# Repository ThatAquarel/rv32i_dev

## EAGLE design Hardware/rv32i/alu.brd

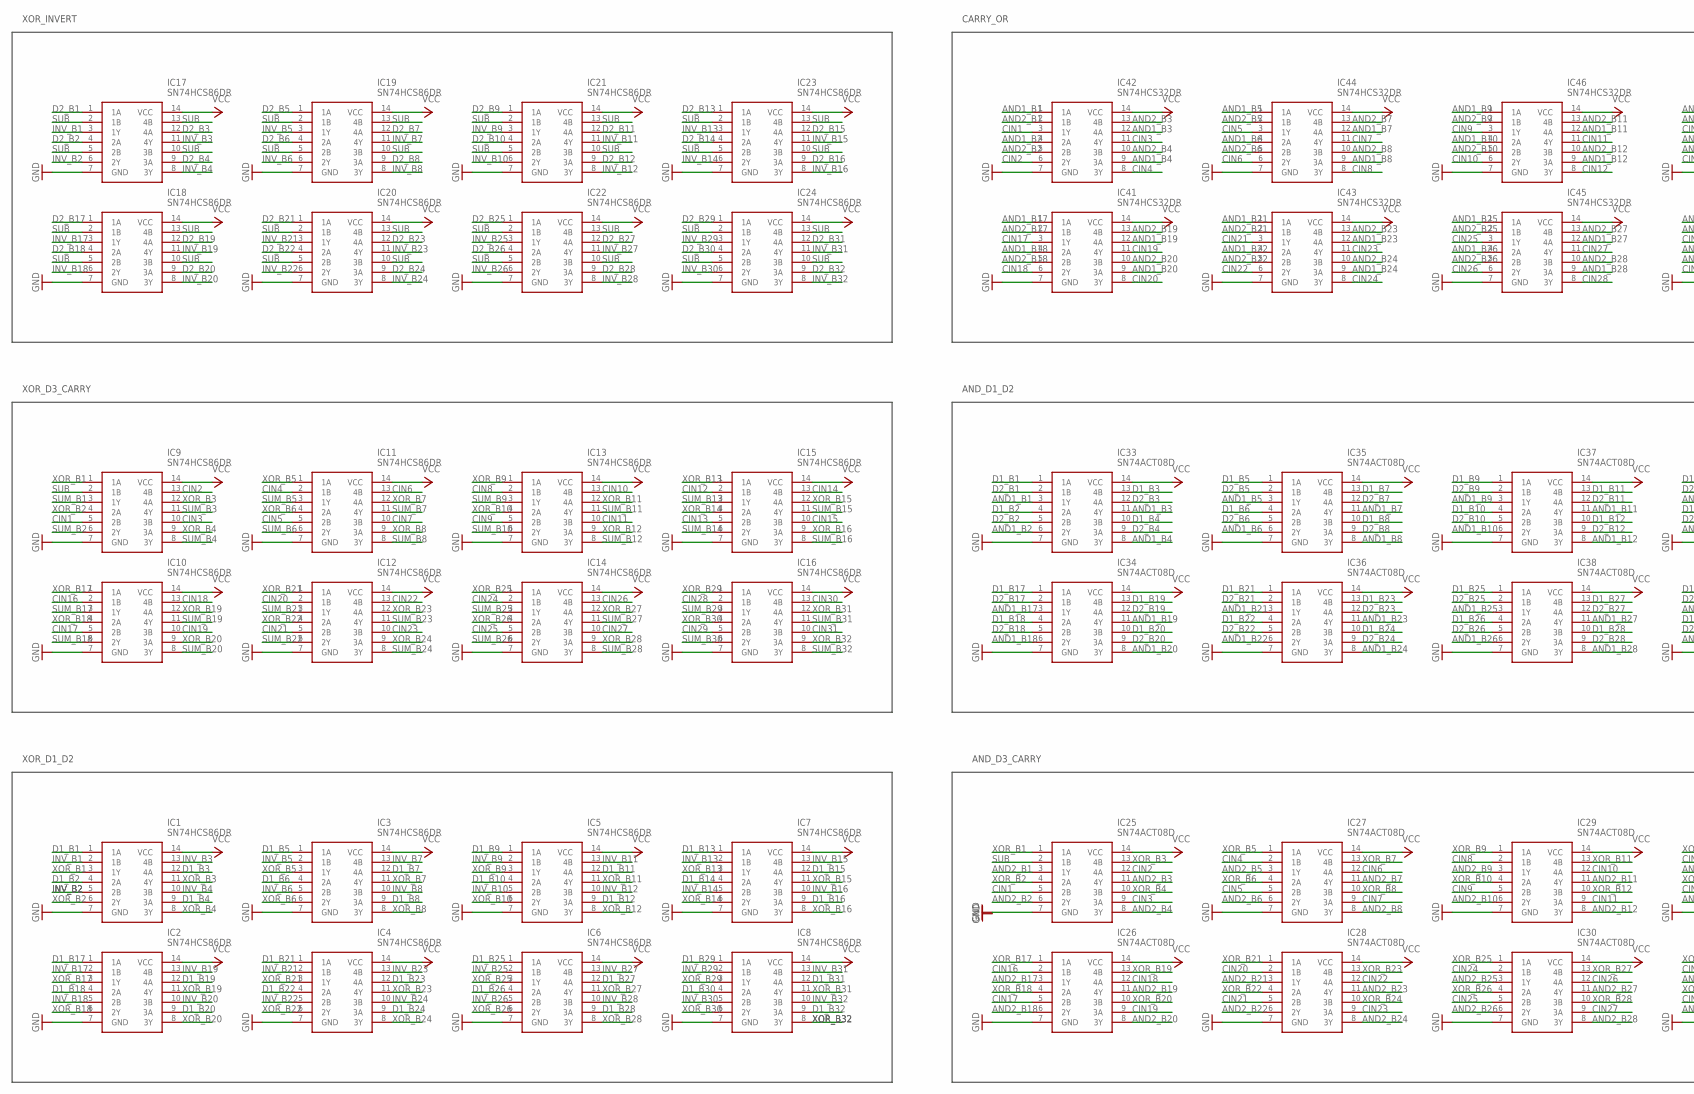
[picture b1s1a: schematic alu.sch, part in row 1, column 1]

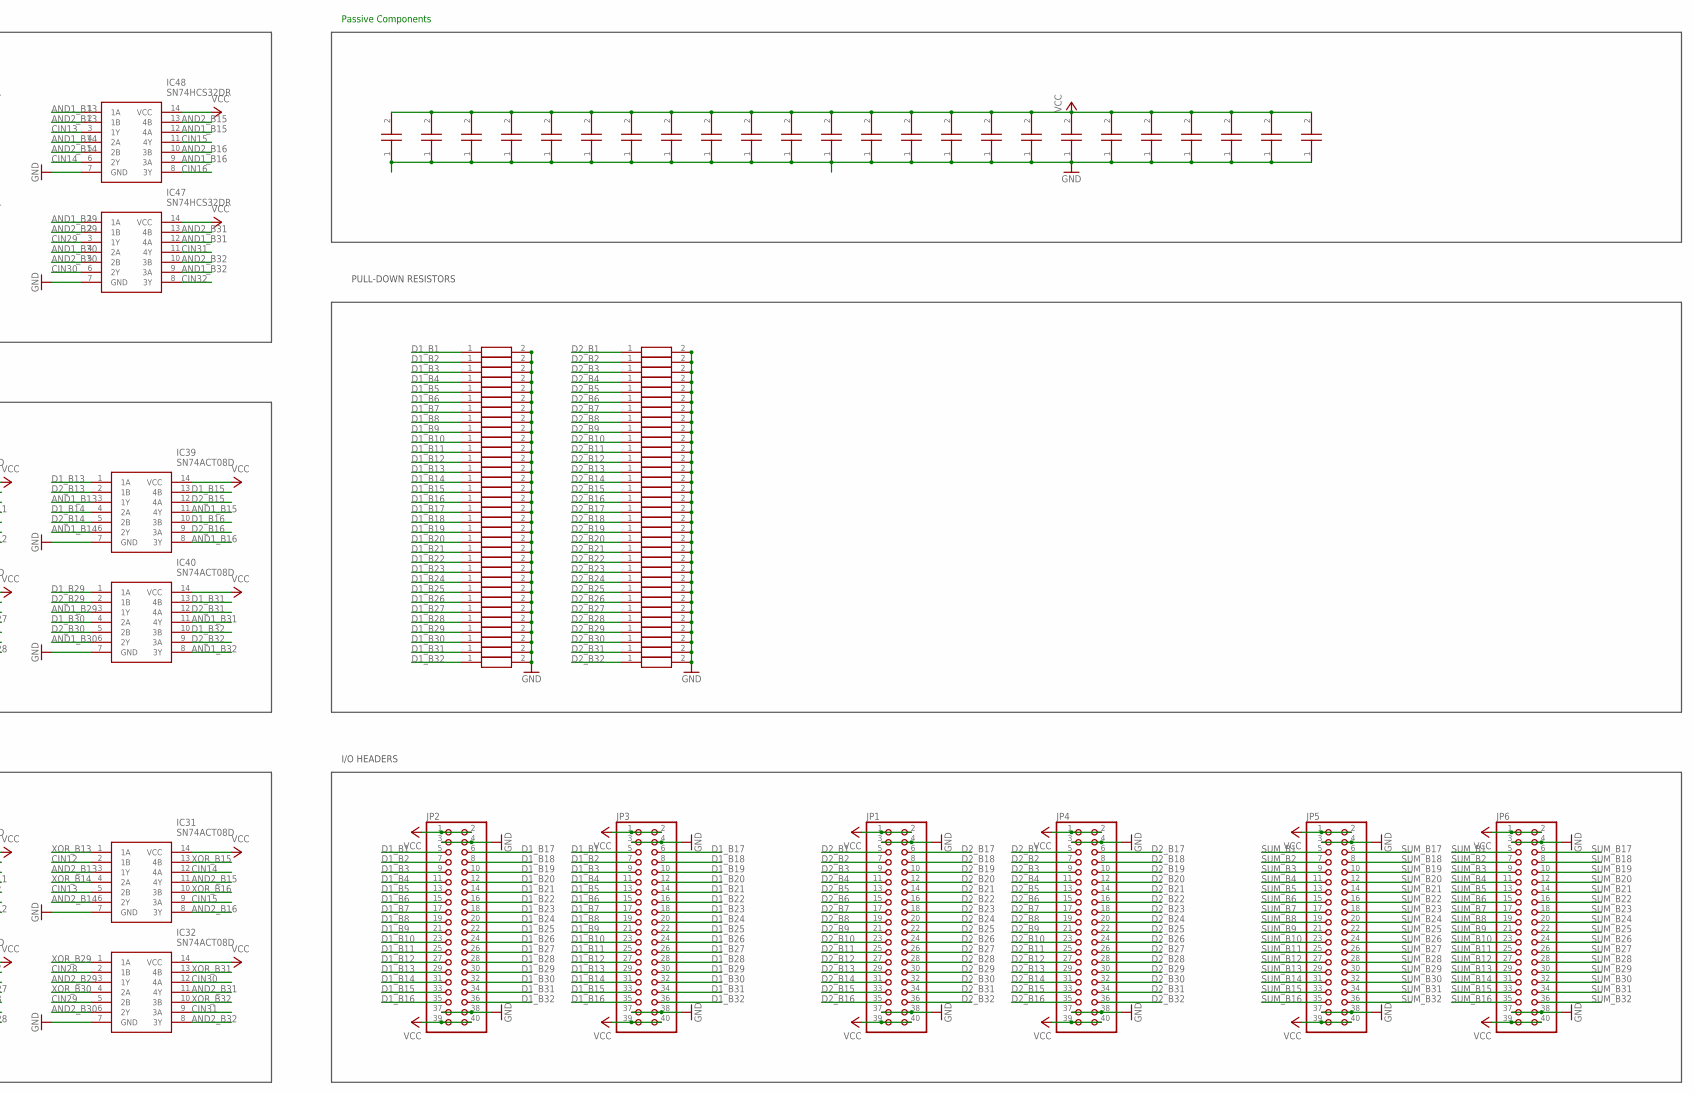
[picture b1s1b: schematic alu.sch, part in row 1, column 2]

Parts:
C1, C2, C3, C4, C5, C6, C7, C8, C9, C10, C11, C12, C13, C14, C15, C16, C17, C18, C19, C20, C21, C22, C23, C24: CC0603KRX7R9BB104; CAPC1608X90N
IC1, IC2, IC3, IC4, IC5, IC6, IC7, IC8, IC9, IC10, IC11, IC12, IC13, IC14, IC15, IC16, IC17, IC18, IC19, IC20, IC21, IC22, IC23, IC24: SN74HCS86DR; SOIC127P600X175-14N
IC25, IC26, IC27, IC28, IC29, IC30, IC31, IC32, IC33, IC34, IC35, IC36, IC37, IC38, IC39, IC40: SN74ACT08D; SOIC127P600X175-14N
IC41, IC42, IC43, IC44, IC45, IC46, IC47, IC48: SN74HCS32DR; SOIC127P600X175-14N
JP1, JP2, JP3, JP4, JP5, JP6: PINHD-2X20; 2X20
R1, R2, R3, R4, R5, R6, R7, R8, R9, R10, R11, R12, R13, R14, R15, R16, R17, R18, R19, R20, R21, R22, R23, R24, R25, R26, R27, R28, R29, R30, R31, R32, R33, R34, R35, R36, R37, R38, R39, R40, R41, R42, R43, R44, R45, R46, R47, R48, R49, R50, R51, R52, R53, R54, R55, R56, R57, R58, R59, R60, R61, R62, R63, R64: RC0603FR-0710KL; RESC1608X55N

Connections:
AND1_B1: IC33.3 (1Y), IC42.1 (1A)
AND1_B2: IC33.6 (2Y), IC42.4 (2A)
AND1_B3: IC33.11 (4Y), IC42.12 (4A)
AND1_B4: IC33.8 (3Y), IC42.9 (3A)
AND1_B5: IC35.3 (1Y), IC44.1 (1A)
AND1_B6: IC35.6 (2Y), IC44.4 (2A)
AND1_B7: IC35.11 (4Y), IC44.12 (4A)
AND1_B8: IC35.8 (3Y), IC44.9 (3A)
AND1_B9: IC37.3 (1Y), IC46.1 (1A)
AND1_B10: IC37.6 (2Y), IC46.4 (2A)
AND1_B11: IC37.11 (4Y), IC46.12 (4A)
AND1_B12: IC37.8 (3Y), IC46.9 (3A)
AND1_B13: IC39.3 (1Y), IC48.1 (1A)
AND1_B14: IC39.6 (2Y), IC48.4 (2A)
AND1_B15: IC39.11 (4Y), IC48.12 (4A)
AND1_B16: IC39.8 (3Y), IC48.9 (3A)
AND1_B17: IC34.3 (1Y), IC41.1 (1A)
AND1_B18: IC34.6 (2Y), IC41.4 (2A)
AND1_B19: IC34.11 (4Y), IC41.12 (4A)
AND1_B20: IC34.8 (3Y), IC41.9 (3A)
AND1_B21: IC36.3 (1Y), IC43.1 (1A)
AND1_B22: IC36.6 (2Y), IC43.4 (2A)
AND1_B23: IC36.11 (4Y), IC43.12 (4A)
AND1_B24: IC36.8 (3Y), IC43.9 (3A)
AND1_B25: IC38.3 (1Y), IC45.1 (1A)
AND1_B26: IC38.6 (2Y), IC45.4 (2A)
AND1_B27: IC38.11 (4Y), IC45.12 (4A)
AND1_B28: IC38.8 (3Y), IC45.9 (3A)
AND1_B29: IC40.3 (1Y), IC47.1 (1A)
AND1_B30: IC40.6 (2Y), IC47.4 (2A)
AND1_B31: IC40.11 (4Y), IC47.12 (4A)
AND1_B32: IC40.8 (3Y), IC47.9 (3A)
AND2_B1: IC25.3 (1Y), IC42.2 (1B)
AND2_B2: IC25.6 (2Y), IC42.5 (2B)
AND2_B3: IC25.11 (4Y), IC42.13 (4B)
AND2_B4: IC25.8 (3Y), IC42.10 (3B)
AND2_B5: IC27.3 (1Y), IC44.2 (1B)
AND2_B6: IC27.6 (2Y), IC44.5 (2B)
AND2_B7: IC27.11 (4Y), IC44.13 (4B)
AND2_B8: IC27.8 (3Y), IC44.10 (3B)
AND2_B9: IC29.3 (1Y), IC46.2 (1B)
AND2_B10: IC29.6 (2Y), IC46.5 (2B)
AND2_B11: IC29.11 (4Y), IC46.13 (4B)
AND2_B12: IC29.8 (3Y), IC46.10 (3B)
AND2_B13: IC31.3 (1Y), IC48.2 (1B)
AND2_B14: IC31.6 (2Y), IC48.5 (2B)
AND2_B15: IC31.11 (4Y), IC48.13 (4B)
AND2_B16: IC31.8 (3Y), IC48.10 (3B)
AND2_B17: IC26.3 (1Y), IC41.2 (1B)
AND2_B18: IC26.6 (2Y), IC41.5 (2B)
AND2_B19: IC26.11 (4Y), IC41.13 (4B)
AND2_B20: IC26.8 (3Y), IC41.10 (3B)
AND2_B21: IC28.3 (1Y), IC43.2 (1B)
AND2_B22: IC28.6 (2Y), IC43.5 (2B)
AND2_B23: IC28.11 (4Y), IC43.13 (4B)
AND2_B24: IC28.8 (3Y), IC43.10 (3B)
AND2_B25: IC30.3 (1Y), IC45.2 (1B)
AND2_B26: IC30.6 (2Y), IC45.5 (2B)
AND2_B27: IC30.11 (4Y), IC45.13 (4B)
AND2_B28: IC30.8 (3Y), IC45.10 (3B)
AND2_B29: IC32.3 (1Y), IC47.2 (1B)
AND2_B30: IC32.6 (2Y), IC47.5 (2B)
AND2_B31: IC32.11 (4Y), IC47.13 (4B)
AND2_B32: IC32.8 (3Y), IC47.10 (3B)
CIN1: IC9.5 (2B), IC25.5 (2B), IC42.3 (1Y)
CIN2: IC9.13 (4B), IC25.12 (4A), IC42.6 (2Y)
CIN3: IC9.10 (3B), IC25.9 (3A), IC42.11 (4Y)
CIN4: IC11.2 (1B), IC27.2 (1B), IC42.8 (3Y)
CIN5: IC11.5 (2B), IC27.5 (2B), IC44.3 (1Y)
CIN6: IC11.13 (4B), IC27.12 (4A), IC44.6 (2Y)
CIN7: IC11.10 (3B), IC27.9 (3A), IC44.11 (4Y)
CIN8: IC13.2 (1B), IC29.2 (1B), IC44.8 (3Y)
CIN9: IC13.5 (2B), IC29.5 (2B), IC46.3 (1Y)
CIN10: IC13.13 (4B), IC29.12 (4A), IC46.6 (2Y)
CIN11: IC13.10 (3B), IC29.9 (3A), IC46.11 (4Y)
CIN12: IC15.2 (1B), IC31.2 (1B), IC46.8 (3Y)
CIN13: IC15.5 (2B), IC31.5 (2B), IC48.3 (1Y)
CIN14: IC15.13 (4B), IC31.12 (4A), IC48.6 (2Y)
CIN15: IC15.10 (3B), IC31.9 (3A), IC48.11 (4Y)
CIN16: IC10.2 (1B), IC26.2 (1B), IC48.8 (3Y)
CIN17: IC10.5 (2B), IC26.5 (2B), IC41.3 (1Y)
CIN18: IC10.13 (4B), IC26.12 (4A), IC41.6 (2Y)
CIN19: IC10.10 (3B), IC26.9 (3A), IC41.11 (4Y)
CIN20: IC12.2 (1B), IC28.2 (1B), IC41.8 (3Y)
CIN21: IC12.5 (2B), IC28.5 (2B), IC43.3 (1Y)
CIN22: IC12.13 (4B), IC28.12 (4A), IC43.6 (2Y)
CIN23: IC12.10 (3B), IC28.9 (3A), IC43.11 (4Y)
CIN24: IC14.2 (1B), IC30.2 (1B), IC43.8 (3Y)
CIN25: IC14.5 (2B), IC30.5 (2B), IC45.3 (1Y)
CIN26: IC14.13 (4B), IC30.12 (4A), IC45.6 (2Y)
CIN27: IC14.10 (3B), IC30.9 (3A), IC45.11 (4Y)
CIN28: IC16.2 (1B), IC32.2 (1B), IC45.8 (3Y)
CIN29: IC16.5 (2B), IC32.5 (2B), IC47.3 (1Y)
CIN30: IC16.13 (4B), IC32.12 (4A), IC47.6 (2Y)
CIN31: IC16.10 (3B), IC32.9 (3A), IC47.11 (4Y)
CIN32: IC47.8 (3Y)
D1_B1: IC1.1 (1A), IC33.1 (1A), JP2.5, JP3.5, R1.1
D1_B2: IC1.4 (2A), IC33.4 (2A), JP2.7, JP3.7, R2.1
D1_B3: IC1.12 (4A), IC33.13 (4B), JP2.9, JP3.9, R3.1
D1_B4: IC1.9 (3A), IC33.10 (3B), JP2.11, JP3.11, R4.1
D1_B5: IC3.1 (1A), IC35.1 (1A), JP2.13, JP3.13, R5.1
D1_B6: IC3.4 (2A), IC35.4 (2A), JP2.15, JP3.15, R6.1
D1_B7: IC3.12 (4A), IC35.13 (4B), JP2.17, JP3.17, R7.1
D1_B8: IC3.9 (3A), IC35.10 (3B), JP2.19, JP3.19, R8.1
D1_B9: IC5.1 (1A), IC37.1 (1A), JP2.21, JP3.21, R9.1
D1_B10: IC5.4 (2A), IC37.4 (2A), JP2.23, JP3.23, R10.1
D1_B11: IC5.12 (4A), IC37.13 (4B), JP2.25, JP3.25, R11.1
D1_B12: IC5.9 (3A), IC37.10 (3B), JP2.27, JP3.27, R12.1
D1_B13: IC7.1 (1A), IC39.1 (1A), JP2.29, JP3.29, R13.1
D1_B14: IC7.4 (2A), IC39.4 (2A), JP2.31, JP3.31, R14.1
D1_B15: IC7.12 (4A), IC39.13 (4B), JP2.33, JP3.33, R15.1
D1_B16: IC7.9 (3A), IC39.10 (3B), JP2.35, JP3.35, R17.1
D1_B17: IC2.1 (1A), IC34.1 (1A), JP2.6, JP3.6, R16.1
D1_B18: IC2.4 (2A), IC34.4 (2A), JP2.8, JP3.8, R18.1
D1_B19: IC2.12 (4A), IC34.13 (4B), JP2.10, JP3.10, R19.1
D1_B20: IC2.9 (3A), IC34.10 (3B), JP2.12, JP3.12, R20.1
D1_B21: IC4.1 (1A), IC36.1 (1A), JP2.14, JP3.14, R21.1
D1_B22: IC4.4 (2A), IC36.4 (2A), JP2.16, JP3.16, R22.1
D1_B23: IC4.12 (4A), IC36.13 (4B), JP2.18, JP3.18, R23.1
D1_B24: IC4.9 (3A), IC36.10 (3B), JP2.20, JP3.20, R24.1
D1_B25: IC6.1 (1A), IC38.1 (1A), JP2.22, JP3.22, R26.1
D1_B26: IC6.4 (2A), IC38.4 (2A), JP2.24, JP3.24, R25.1
D1_B27: IC6.12 (4A), IC38.13 (4B), JP2.26, JP3.26, R27.1
D1_B28: IC6.9 (3A), IC38.10 (3B), JP2.28, JP3.28, R28.1
D1_B29: IC8.1 (1A), IC40.1 (1A), JP2.30, JP3.30, R29.1
D1_B30: IC8.4 (2A), IC40.4 (2A), JP2.32, JP3.32, R30.1
D1_B31: IC8.12 (4A), IC40.13 (4B), JP2.34, JP3.34, R31.1
D1_B32: IC8.9 (3A), IC40.10 (3B), JP2.36, JP3.36, R32.1
D2_B1: IC17.1 (1A), IC33.2 (1B), JP1.5, JP4.5, R33.1
D2_B2: IC17.4 (2A), IC33.5 (2B), JP1.7, JP4.7, R34.1
D2_B3: IC17.12 (4A), IC33.12 (4A), JP1.9, JP4.9, R35.1
D2_B4: IC17.9 (3A), IC33.9 (3A), JP1.11, JP4.11, R36.1
D2_B5: IC19.1 (1A), IC35.2 (1B), JP1.13, JP4.13, R37.1
D2_B6: IC19.4 (2A), IC35.5 (2B), JP1.15, JP4.15, R38.1
D2_B7: IC19.12 (4A), IC35.12 (4A), JP1.17, JP4.17, R39.1
D2_B8: IC19.9 (3A), IC35.9 (3A), JP1.19, JP4.19, R40.1
D2_B9: IC21.1 (1A), IC37.2 (1B), JP1.21, JP4.21, R41.1
D2_B10: IC21.4 (2A), IC37.5 (2B), JP1.23, JP4.23, R42.1
D2_B11: IC21.12 (4A), IC37.12 (4A), JP1.25, JP4.25, R43.1
D2_B12: IC21.9 (3A), IC37.9 (3A), JP1.27, JP4.27, R44.1
D2_B13: IC23.1 (1A), IC39.2 (1B), JP1.29, JP4.29, R45.1
D2_B14: IC23.4 (2A), IC39.5 (2B), JP1.31, JP4.31, R46.1
D2_B15: IC23.12 (4A), IC39.12 (4A), JP1.33, JP4.33, R47.1
D2_B16: IC23.9 (3A), IC39.9 (3A), JP1.35, JP4.35, R49.1
D2_B17: IC18.1 (1A), IC34.2 (1B), JP1.6, JP4.6, R48.1
D2_B18: IC18.4 (2A), IC34.5 (2B), JP1.8, JP4.8, R50.1
D2_B19: IC18.12 (4A), IC34.12 (4A), JP1.10, JP4.10, R51.1
D2_B20: IC18.9 (3A), IC34.9 (3A), JP1.12, JP4.12, R52.1
D2_B21: IC20.1 (1A), IC36.2 (1B), JP1.14, JP4.14, R53.1
D2_B22: IC20.4 (2A), IC36.5 (2B), JP1.16, JP4.16, R54.1
D2_B23: IC20.12 (4A), IC36.12 (4A), JP1.18, JP4.18, R55.1
D2_B24: IC20.9 (3A), IC36.9 (3A), JP1.20, JP4.20, R56.1
D2_B25: IC22.1 (1A), IC38.2 (1B), JP1.22, JP4.22, R58.1
D2_B26: IC22.4 (2A), IC38.5 (2B), JP1.24, JP4.24, R57.1
D2_B27: IC22.12 (4A), IC38.12 (4A), JP1.26, JP4.26, R59.1
D2_B28: IC22.9 (3A), IC38.9 (3A), JP1.28, JP4.28, R60.1
D2_B29: IC24.1 (1A), IC40.2 (1B), JP1.30, JP4.30, R61.1
D2_B30: IC24.4 (2A), IC40.5 (2B), JP1.32, JP4.32, R62.1
D2_B31: IC24.12 (4A), IC40.12 (4A), JP1.34, JP4.34, R63.1
D2_B32: IC24.9 (3A), IC40.9 (3A), JP1.36, JP4.36, R64.1
GND: C1.1, C2.1, C3.1, C4.1, C5.1, C6.1, C7.1, C8.1, C9.1, C10.1, C11.1, C12.1, C13.1, C14.1, C15.1, C16.1, C17.1, C18.1, C19.1, C20.1, C21.1, C22.1, C23.1, C24.1, IC1.7 (GND), IC2.7 (GND), IC3.7 (GND), IC4.7 (GND), IC5.7 (GND), IC6.7 (GND), IC7.7 (GND), IC8.7 (GND), IC9.7 (GND), IC10.7 (GND), IC11.7 (GND), IC12.7 (GND), IC13.7 (GND), IC14.7 (GND), IC15.7 (GND), IC16.7 (GND), IC17.7 (GND), IC18.7 (GND), IC19.7 (GND), IC20.7 (GND), IC21.7 (GND), IC22.7 (GND), IC23.7 (GND), IC24.7 (GND), IC25.7 (GND), IC26.7 (GND), IC27.7 (GND), IC28.7 (GND), IC29.7 (GND), IC30.7 (GND), IC31.7 (GND), IC32.7 (GND), IC33.7 (GND), IC34.7 (GND), IC35.7 (GND), IC36.7 (GND), IC37.7 (GND), IC38.7 (GND), IC39.7 (GND), IC40.7 (GND), IC41.7 (GND), IC42.7 (GND), IC43.7 (GND), IC44.7 (GND), IC45.7 (GND), IC46.7 (GND), IC47.7 (GND), IC48.7 (GND), JP1.3, JP1.4, JP1.37, JP1.38, JP2.3, JP2.4, JP2.37, JP2.38, JP3.3, JP3.4, JP3.37, JP3.38, JP4.3, JP4.4, JP4.37, JP4.38, JP5.3, JP5.4, JP5.37, JP5.38, JP6.3, JP6.4, JP6.37, JP6.38, R1.2, R2.2, R3.2, R4.2, R5.2, R6.2, R7.2, R8.2, R9.2, R10.2, R11.2, R12.2, R13.2, R14.2, R15.2, R16.2, R17.2, R18.2, R19.2, R20.2, R21.2, R22.2, R23.2, R24.2, R25.2, R26.2, R27.2, R28.2, R29.2, R30.2, R31.2, R32.2, R33.2, R34.2, R35.2, R36.2, R37.2, R38.2, R39.2, R40.2, R41.2, R42.2, R43.2, R44.2, R45.2, R46.2, R47.2, R48.2, R49.2, R50.2, R51.2, R52.2, R53.2, R54.2, R55.2, R56.2, R57.2, R58.2, R59.2, R60.2, R61.2, R62.2, R63.2, R64.2
INV_B1: IC1.2 (1B), IC17.3 (1Y)
INV_B2: IC1.5 (2B), IC17.6 (2Y)
INV_B3: IC1.13 (4B), IC17.11 (4Y)
INV_B4: IC1.10 (3B), IC17.8 (3Y)
INV_B5: IC3.2 (1B), IC19.3 (1Y)
INV_B6: IC3.5 (2B), IC19.6 (2Y)
INV_B7: IC3.13 (4B), IC19.11 (4Y)
INV_B8: IC3.10 (3B), IC19.8 (3Y)
INV_B9: IC5.2 (1B), IC21.3 (1Y)
INV_B10: IC5.5 (2B), IC21.6 (2Y)
INV_B11: IC5.13 (4B), IC21.11 (4Y)
INV_B12: IC5.10 (3B), IC21.8 (3Y)
INV_B13: IC7.2 (1B), IC23.3 (1Y)
INV_B14: IC7.5 (2B), IC23.6 (2Y)
INV_B15: IC7.13 (4B), IC23.11 (4Y)
INV_B16: IC7.10 (3B), IC23.8 (3Y)
INV_B17: IC2.2 (1B), IC18.3 (1Y)
INV_B18: IC2.5 (2B), IC18.6 (2Y)
INV_B19: IC2.13 (4B), IC18.11 (4Y)
INV_B20: IC2.10 (3B), IC18.8 (3Y)
INV_B21: IC4.2 (1B), IC20.3 (1Y)
INV_B22: IC4.5 (2B), IC20.6 (2Y)
INV_B23: IC4.13 (4B), IC20.11 (4Y)
INV_B24: IC4.10 (3B), IC20.8 (3Y)
INV_B25: IC6.2 (1B), IC22.3 (1Y)
INV_B26: IC6.5 (2B), IC22.6 (2Y)
INV_B27: IC6.13 (4B), IC22.11 (4Y)
INV_B28: IC6.10 (3B), IC22.8 (3Y)
INV_B29: IC8.2 (1B), IC24.3 (1Y)
INV_B30: IC8.5 (2B), IC24.6 (2Y)
INV_B31: IC8.13 (4B), IC24.11 (4Y)
INV_B32: IC8.10 (3B), IC24.8 (3Y)
SUB: IC9.2 (1B), IC17.2 (1B), IC17.5 (2B), IC17.10 (3B), IC17.13 (4B), IC18.2 (1B), IC18.5 (2B), IC18.10 (3B), IC18.13 (4B), IC19.2 (1B), IC19.5 (2B), IC19.10 (3B), IC19.13 (4B), IC20.2 (1B), IC20.5 (2B), IC20.10 (3B), IC20.13 (4B), IC21.2 (1B), IC21.5 (2B), IC21.10 (3B), IC21.13 (4B), IC22.2 (1B), IC22.5 (2B), IC22.10 (3B), IC22.13 (4B), IC23.2 (1B), IC23.5 (2B), IC23.10 (3B), IC23.13 (4B), IC24.2 (1B), IC24.5 (2B), IC24.10 (3B), IC24.13 (4B), IC25.2 (1B)
SUM_B1: IC9.3 (1Y), JP5.5, JP6.5
SUM_B2: IC9.6 (2Y), JP5.7, JP6.7
SUM_B3: IC9.11 (4Y), JP5.9, JP6.9
SUM_B4: IC9.8 (3Y), JP5.11, JP6.11
SUM_B5: IC11.3 (1Y), JP5.13, JP6.13
SUM_B6: IC11.6 (2Y), JP5.15, JP6.15
SUM_B7: IC11.11 (4Y), JP5.17, JP6.17
SUM_B8: IC11.8 (3Y), JP5.19, JP6.19
SUM_B9: IC13.3 (1Y), JP5.21, JP6.21
SUM_B10: IC13.6 (2Y), JP5.23, JP6.23
SUM_B11: IC13.11 (4Y), JP5.25, JP6.25
SUM_B12: IC13.8 (3Y), JP5.27, JP6.27
SUM_B13: IC15.3 (1Y), JP5.29, JP6.29
SUM_B14: IC15.6 (2Y), JP5.31, JP6.31
SUM_B15: IC15.11 (4Y), JP5.33, JP6.33
SUM_B16: IC15.8 (3Y), JP5.35, JP6.35
SUM_B17: IC10.3 (1Y), JP5.6, JP6.6
SUM_B18: IC10.6 (2Y), JP5.8, JP6.8
SUM_B19: IC10.11 (4Y), JP5.10, JP6.10
SUM_B20: IC10.8 (3Y), JP5.12, JP6.12
SUM_B21: IC12.3 (1Y), JP5.14, JP6.14
SUM_B22: IC12.6 (2Y), JP5.16, JP6.16
SUM_B23: IC12.11 (4Y), JP5.18, JP6.18
SUM_B24: IC12.8 (3Y), JP5.20, JP6.20
SUM_B25: IC14.3 (1Y), JP5.22, JP6.22
SUM_B26: IC14.6 (2Y), JP5.24, JP6.24
SUM_B27: IC14.11 (4Y), JP5.26, JP6.26
SUM_B28: IC14.8 (3Y), JP5.28, JP6.28
SUM_B29: IC16.3 (1Y), JP5.30, JP6.30
SUM_B30: IC16.6 (2Y), JP5.32, JP6.32
SUM_B31: IC16.11 (4Y), JP5.34, JP6.34
SUM_B32: IC16.8 (3Y), JP5.36, JP6.36
VCC: C1.2, C2.2, C3.2, C4.2, C5.2, C6.2, C7.2, C8.2, C9.2, C10.2, C11.2, C12.2, C13.2, C14.2, C15.2, C16.2, C17.2, C18.2, C19.2, C20.2, C21.2, C22.2, C23.2, C24.2, IC1.14 (VCC), IC2.14 (VCC), IC3.14 (VCC), IC4.14 (VCC), IC5.14 (VCC), IC6.14 (VCC), IC7.14 (VCC), IC8.14 (VCC), IC9.14 (VCC), IC10.14 (VCC), IC11.14 (VCC), IC12.14 (VCC), IC13.14 (VCC), IC14.14 (VCC), IC15.14 (VCC), IC16.14 (VCC), IC17.14 (VCC), IC18.14 (VCC), IC19.14 (VCC), IC20.14 (VCC), IC21.14 (VCC), IC22.14 (VCC), IC23.14 (VCC), IC24.14 (VCC), IC25.14 (VCC), IC26.14 (VCC), IC27.14 (VCC), IC28.14 (VCC), IC29.14 (VCC), IC30.14 (VCC), IC31.14 (VCC), IC32.14 (VCC), IC33.14 (VCC), IC34.14 (VCC), IC35.14 (VCC), IC36.14 (VCC), IC37.14 (VCC), IC38.14 (VCC), IC39.14 (VCC), IC40.14 (VCC), IC41.14 (VCC), IC42.14 (VCC), IC43.14 (VCC), IC44.14 (VCC), IC45.14 (VCC), IC46.14 (VCC), IC47.14 (VCC), IC48.14 (VCC), JP1.1, JP1.2, JP1.39, JP1.40, JP2.1, JP2.2, JP2.39, JP2.40, JP3.1, JP3.2, JP3.39, JP3.40, JP4.1, JP4.2, JP4.39, JP4.40, JP5.1, JP5.2, JP5.39, JP5.40, JP6.1, JP6.2, JP6.39, JP6.40
XOR_B1: IC1.3 (1Y), IC9.1 (1A), IC25.1 (1A)
XOR_B2: IC1.6 (2Y), IC9.4 (2A), IC25.4 (2A)
XOR_B3: IC1.11 (4Y), IC9.12 (4A), IC25.13 (4B)
XOR_B4: IC1.8 (3Y), IC9.9 (3A), IC25.10 (3B)
XOR_B5: IC3.3 (1Y), IC11.1 (1A), IC27.1 (1A)
XOR_B6: IC3.6 (2Y), IC11.4 (2A), IC27.4 (2A)
XOR_B7: IC3.11 (4Y), IC11.12 (4A), IC27.13 (4B)
XOR_B8: IC3.8 (3Y), IC11.9 (3A), IC27.10 (3B)
XOR_B9: IC5.3 (1Y), IC13.1 (1A), IC29.1 (1A)
XOR_B10: IC5.6 (2Y), IC13.4 (2A), IC29.4 (2A)
XOR_B11: IC5.11 (4Y), IC13.12 (4A), IC29.13 (4B)
XOR_B12: IC5.8 (3Y), IC13.9 (3A), IC29.10 (3B)
XOR_B13: IC7.3 (1Y), IC15.1 (1A), IC31.1 (1A)
XOR_B14: IC7.6 (2Y), IC15.4 (2A), IC31.4 (2A)
XOR_B15: IC7.11 (4Y), IC15.12 (4A), IC31.13 (4B)
XOR_B16: IC7.8 (3Y), IC15.9 (3A), IC31.10 (3B)
XOR_B17: IC2.3 (1Y), IC10.1 (1A), IC26.1 (1A)
XOR_B18: IC2.6 (2Y), IC10.4 (2A), IC26.4 (2A)
XOR_B19: IC2.11 (4Y), IC10.12 (4A), IC26.13 (4B)
XOR_B20: IC2.8 (3Y), IC10.9 (3A), IC26.10 (3B)
XOR_B21: IC4.3 (1Y), IC12.1 (1A), IC28.1 (1A)
XOR_B22: IC4.6 (2Y), IC12.4 (2A), IC28.4 (2A)
XOR_B23: IC4.11 (4Y), IC12.12 (4A), IC28.13 (4B)
XOR_B24: IC4.8 (3Y), IC12.9 (3A), IC28.10 (3B)
XOR_B25: IC6.3 (1Y), IC14.1 (1A), IC30.1 (1A)
XOR_B26: IC6.6 (2Y), IC14.4 (2A), IC30.4 (2A)
XOR_B27: IC6.11 (4Y), IC14.12 (4A), IC30.13 (4B)
XOR_B28: IC6.8 (3Y), IC14.9 (3A), IC30.10 (3B)
XOR_B29: IC8.3 (1Y), IC16.1 (1A), IC32.1 (1A)
XOR_B30: IC8.6 (2Y), IC16.4 (2A), IC32.4 (2A)
XOR_B31: IC8.11 (4Y), IC16.12 (4A), IC32.13 (4B)
XOR_B32: IC8.8 (3Y), IC16.9 (3A), IC32.10 (3B)

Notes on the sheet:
XOR_D1_D2
XOR_D3_CARRY
XOR_INVERT
AND_D3_CARRY
I/O HEADERS
AND_D1_D2
CARRY_OR
PULL-DOWN RESISTORS
Passive Components

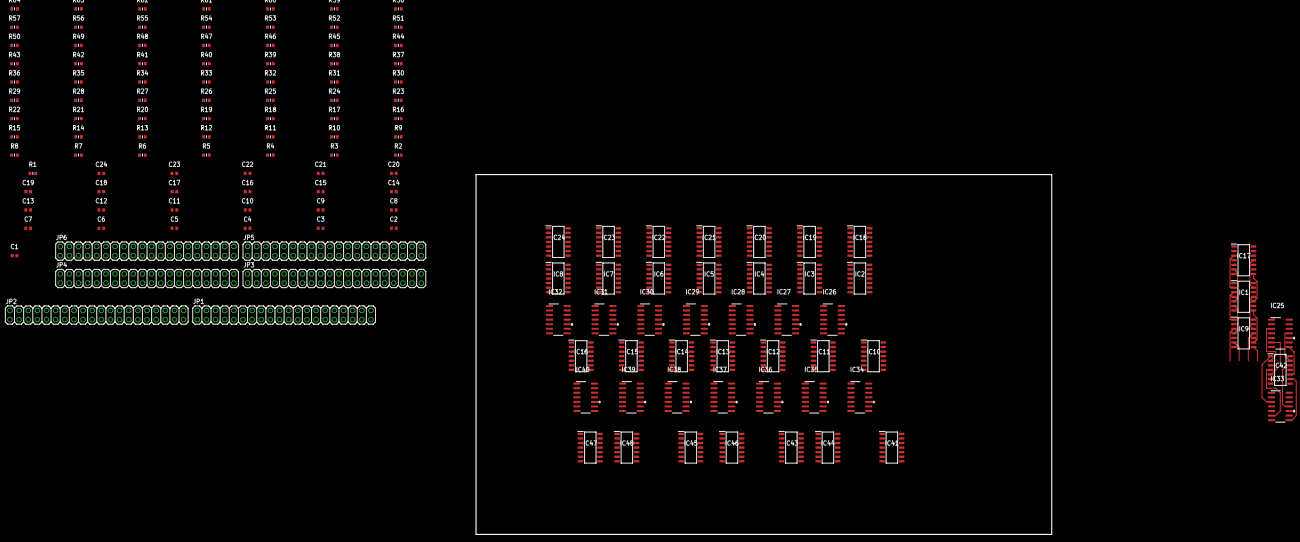
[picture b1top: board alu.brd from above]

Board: 2 copper layers, 160.0 x 100.0 mm, 142 parts (0 on the bottom side), 258 nets.

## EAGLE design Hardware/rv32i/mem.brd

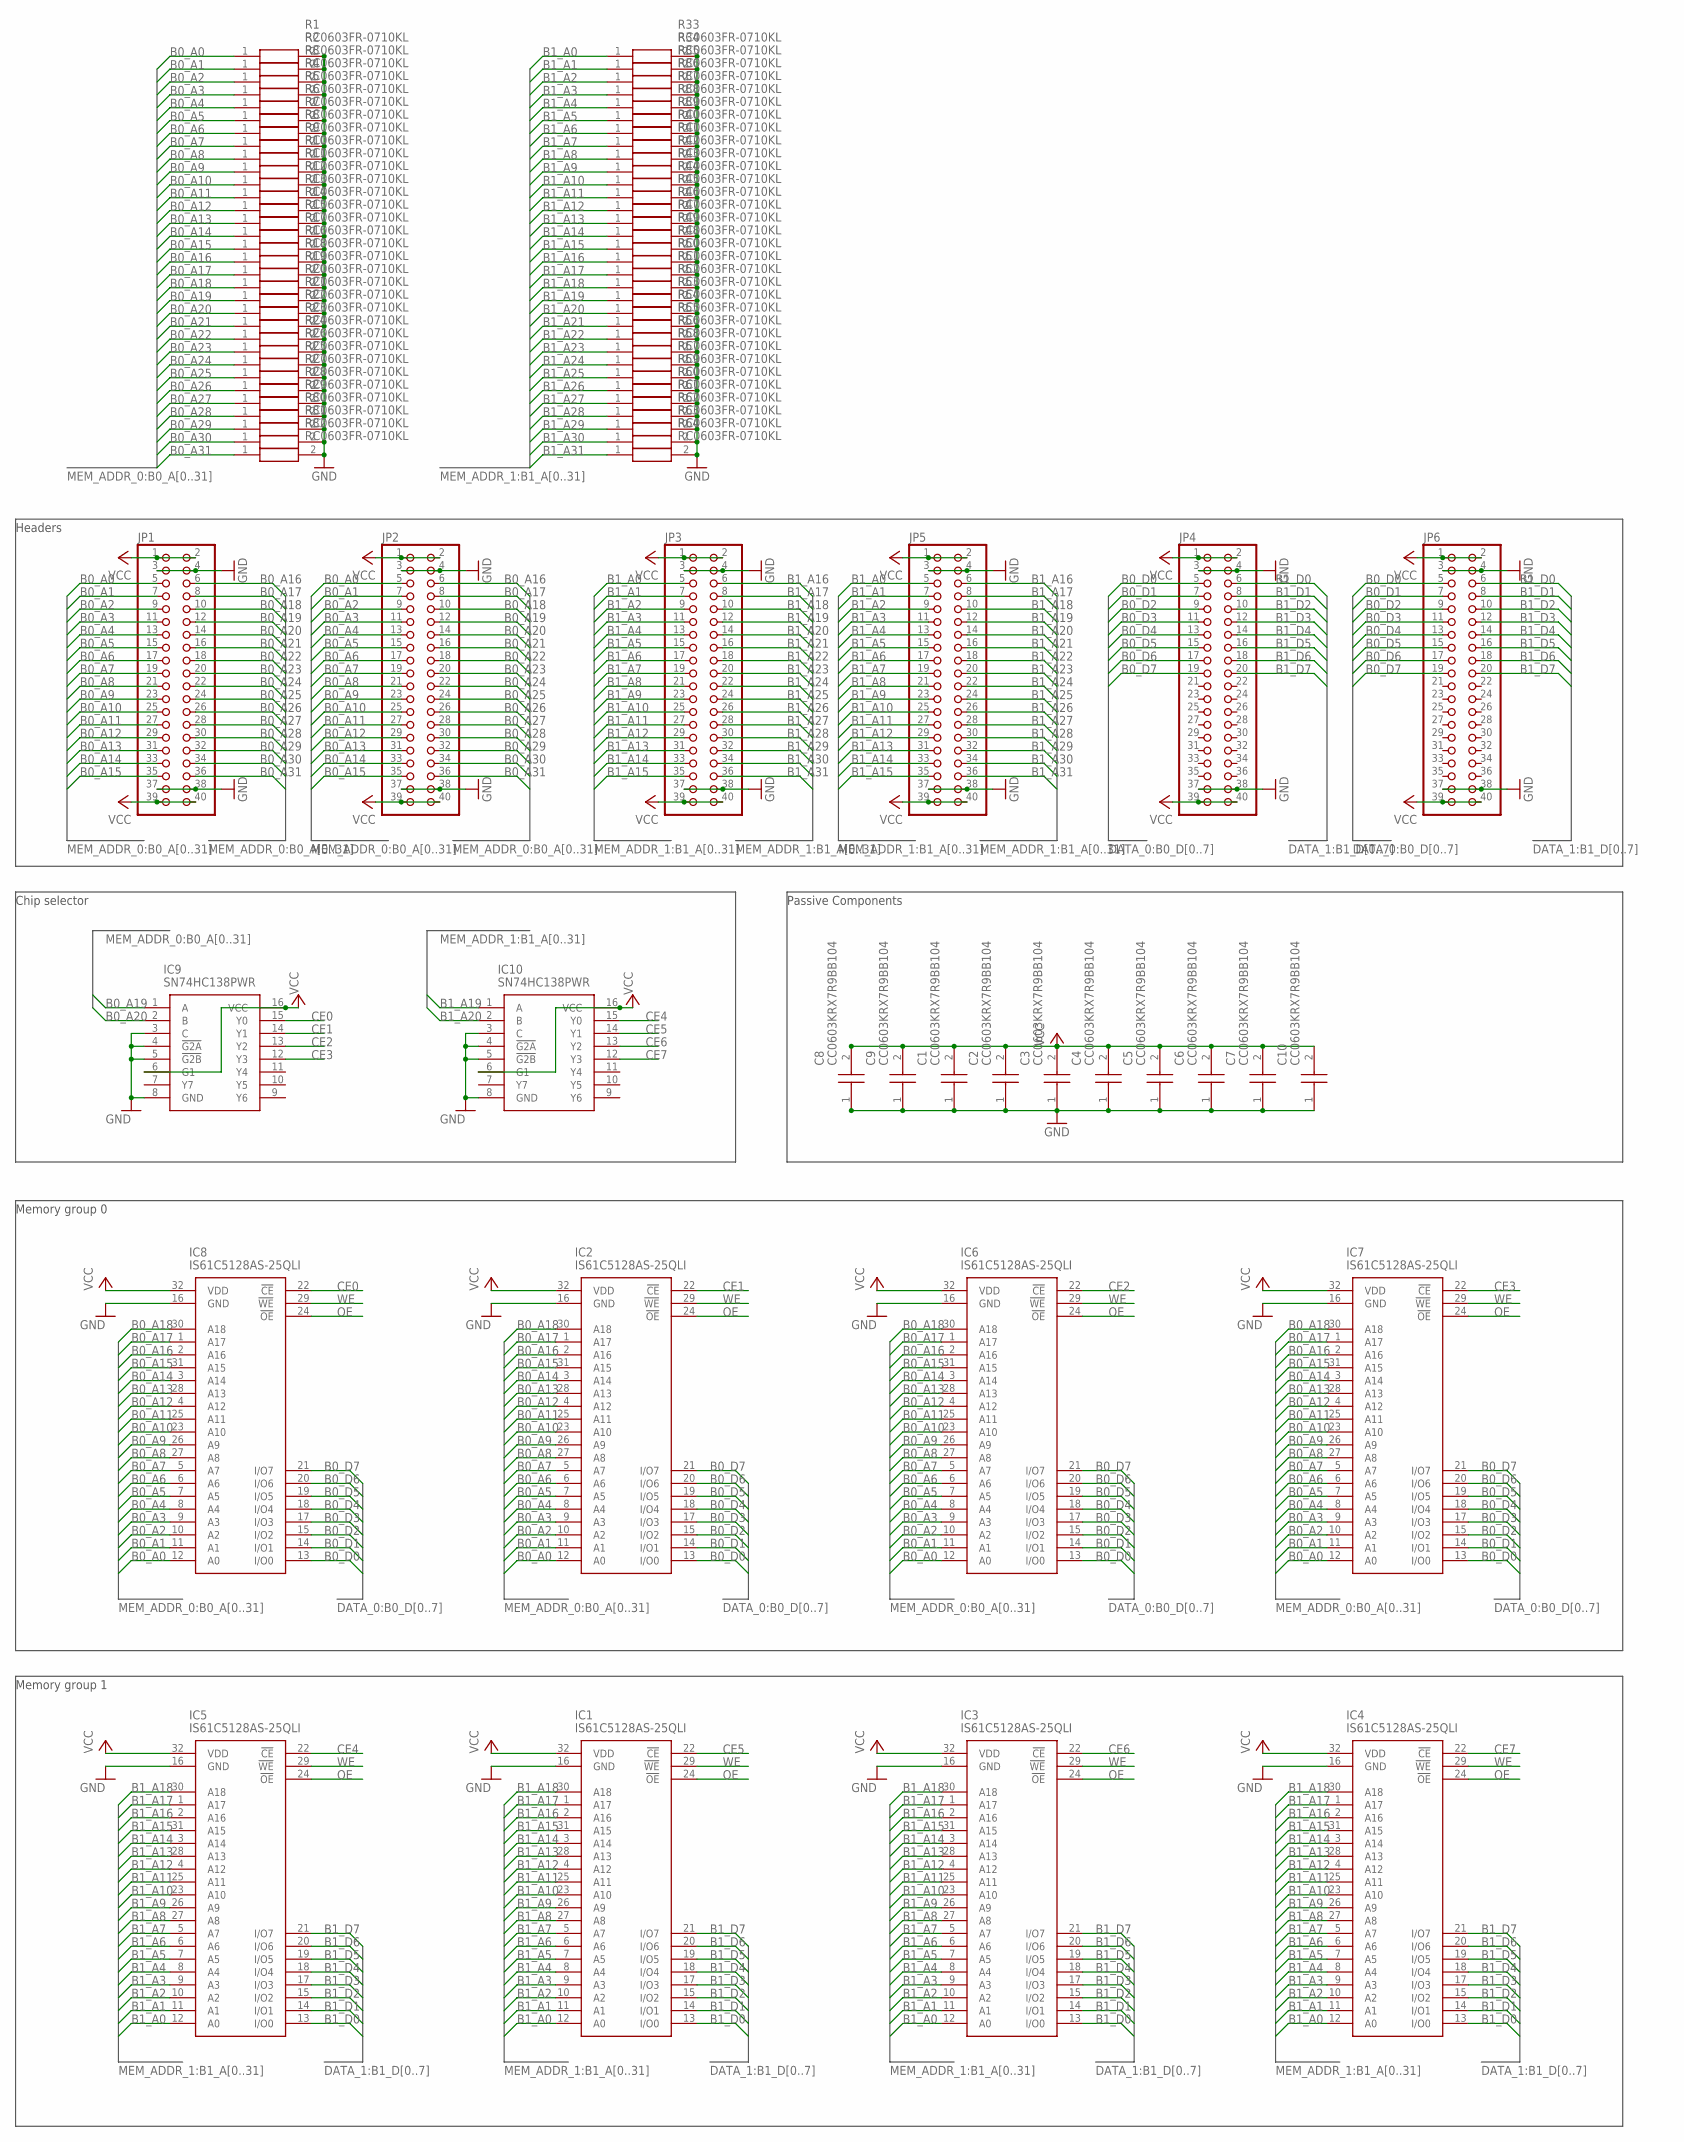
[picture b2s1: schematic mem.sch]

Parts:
C1, C2, C3, C4, C5, C6, C7, C8, C9, C10: CC0603KRX7R9BB104; CAPC1608X90N
IC1, IC2, IC3, IC4, IC5, IC6, IC7, IC8: IS61C5128AS-25QLI; SOIC127P1412X305-32N
IC9, IC10: SN74HC138PWR; SOP65P640X120-16N
JP1, JP2, JP3, JP4, JP5, JP6: PINHD-2X20; 2X20
R1, R2, R3, R4, R5, R6, R7, R8, R9, R10, R11, R12, R13, R14, R15, R16, R17, R18, R19, R20, R21, R22, R23, R24, R25, R26, R27, R28, R29, R30, R31, R32, R33, R34, R35, R36, R37, R38, R39, R40, R41, R42, R43, R44, R45, R46, R47, R48, R49, R50, R51, R52, R53, R54, R55, R56, R57, R58, R59, R60, R61, R62, R63, R64: RC0603FR-0710KL; RESC1608X55N

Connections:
B0_A0: IC2.12 (A0), IC6.12 (A0), IC7.12 (A0), IC8.12 (A0), JP1.5, JP2.5, R1.1
B0_A1: IC2.11 (A1), IC6.11 (A1), IC7.11 (A1), IC8.11 (A1), JP1.7, JP2.7, R2.1
B0_A2: IC2.10 (A2), IC6.10 (A2), IC7.10 (A2), IC8.10 (A2), JP1.9, JP2.9, R3.1
B0_A3: IC2.9 (A3), IC6.9 (A3), IC7.9 (A3), IC8.9 (A3), JP1.11, JP2.11, R4.1
B0_A4: IC2.8 (A4), IC6.8 (A4), IC7.8 (A4), IC8.8 (A4), JP1.13, JP2.13, R5.1
B0_A5: IC2.7 (A5), IC6.7 (A5), IC7.7 (A5), IC8.7 (A5), JP1.15, JP2.15, R6.1
B0_A6: IC2.6 (A6), IC6.6 (A6), IC7.6 (A6), IC8.6 (A6), JP1.17, JP2.17, R7.1
B0_A7: IC2.5 (A7), IC6.5 (A7), IC7.5 (A7), IC8.5 (A7), JP1.19, JP2.19, R8.1
B0_A8: IC2.27 (A8), IC6.27 (A8), IC7.27 (A8), IC8.27 (A8), JP1.21, JP2.21, R9.1
B0_A9: IC2.26 (A9), IC6.26 (A9), IC7.26 (A9), IC8.26 (A9), JP1.23, JP2.23, R10.1
B0_A10: IC2.23 (A10), IC6.23 (A10), IC7.23 (A10), IC8.23 (A10), JP1.25, JP2.25, R11.1
B0_A11: IC2.25 (A11), IC6.25 (A11), IC7.25 (A11), IC8.25 (A11), JP1.27, JP2.27, R12.1
B0_A12: IC2.4 (A12), IC6.4 (A12), IC7.4 (A12), IC8.4 (A12), JP1.29, JP2.29, R13.1
B0_A13: IC2.28 (A13), IC6.28 (A13), IC7.28 (A13), IC8.28 (A13), JP1.31, JP2.31, R14.1
B0_A14: IC2.3 (A14), IC6.3 (A14), IC7.3 (A14), IC8.3 (A14), JP1.33, JP2.33, R15.1
B0_A15: IC2.31 (A15), IC6.31 (A15), IC7.31 (A15), IC8.31 (A15), JP1.35, JP2.35, R17.1
B0_A16: IC2.2 (A16), IC6.2 (A16), IC7.2 (A16), IC8.2 (A16), JP1.6, JP2.6, R16.1
B0_A17: IC2.1 (A17), IC6.1 (A17), IC7.1 (A17), IC8.1 (A17), JP1.8, JP2.8, R18.1
B0_A18: IC2.30 (A18), IC6.30 (A18), IC7.30 (A18), IC8.30 (A18), JP1.10, JP2.10, R19.1
B0_A19: IC9.1 (A), JP1.12, JP2.12, R20.1
B0_A20: IC9.2 (B), JP1.14, JP2.14, R21.1
B0_A21: JP1.16, JP2.16, R22.1
B0_A22: JP1.18, JP2.18, R23.1
B0_A23: JP1.20, JP2.20, R24.1
B0_A24: JP1.22, JP2.22, R26.1
B0_A25: JP1.24, JP2.24, R25.1
B0_A26: JP1.26, JP2.26, R27.1
B0_A27: JP1.28, JP2.28, R28.1
B0_A28: JP1.30, JP2.30, R29.1
B0_A29: JP1.32, JP2.32, R30.1
B0_A30: JP1.34, JP2.34, R31.1
B0_A31: JP1.36, JP2.36, R32.1
B0_D0: IC2.13 (I/O0), IC6.13 (I/O0), IC7.13 (I/O0), IC8.13 (I/O0), JP4.5, JP6.5
B0_D1: IC2.14 (I/O1), IC6.14 (I/O1), IC7.14 (I/O1), IC8.14 (I/O1), JP4.7, JP6.7
B0_D2: IC2.15 (I/O2), IC6.15 (I/O2), IC7.15 (I/O2), IC8.15 (I/O2), JP4.9, JP6.9
B0_D3: IC2.17 (I/O3), IC6.17 (I/O3), IC7.17 (I/O3), IC8.17 (I/O3), JP4.11, JP6.11
B0_D4: IC2.18 (I/O4), IC6.18 (I/O4), IC7.18 (I/O4), IC8.18 (I/O4), JP4.13, JP6.13
B0_D5: IC2.19 (I/O5), IC6.19 (I/O5), IC7.19 (I/O5), IC8.19 (I/O5), JP4.15, JP6.15
B0_D6: IC2.20 (I/O6), IC6.20 (I/O6), IC7.20 (I/O6), IC8.20 (I/O6), JP4.17, JP6.17
B0_D7: IC2.21 (I/O7), IC6.21 (I/O7), IC7.21 (I/O7), IC8.21 (I/O7), JP4.19, JP6.19
B1_A0: IC1.12 (A0), IC3.12 (A0), IC4.12 (A0), IC5.12 (A0), JP3.5, JP5.5, R33.1
B1_A1: IC1.11 (A1), IC3.11 (A1), IC4.11 (A1), IC5.11 (A1), JP3.7, JP5.7, R34.1
B1_A2: IC1.10 (A2), IC3.10 (A2), IC4.10 (A2), IC5.10 (A2), JP3.9, JP5.9, R35.1
B1_A3: IC1.9 (A3), IC3.9 (A3), IC4.9 (A3), IC5.9 (A3), JP3.11, JP5.11, R36.1
B1_A4: IC1.8 (A4), IC3.8 (A4), IC4.8 (A4), IC5.8 (A4), JP3.13, JP5.13, R37.1
B1_A5: IC1.7 (A5), IC3.7 (A5), IC4.7 (A5), IC5.7 (A5), JP3.15, JP5.15, R38.1
B1_A6: IC1.6 (A6), IC3.6 (A6), IC4.6 (A6), IC5.6 (A6), JP3.17, JP5.17, R39.1
B1_A7: IC1.5 (A7), IC3.5 (A7), IC4.5 (A7), IC5.5 (A7), JP3.19, JP5.19, R40.1
B1_A8: IC1.27 (A8), IC3.27 (A8), IC4.27 (A8), IC5.27 (A8), JP3.21, JP5.21, R41.1
B1_A9: IC1.26 (A9), IC3.26 (A9), IC4.26 (A9), IC5.26 (A9), JP3.23, JP5.23, R42.1
B1_A10: IC1.23 (A10), IC3.23 (A10), IC4.23 (A10), IC5.23 (A10), JP3.25, JP5.25, R43.1
B1_A11: IC1.25 (A11), IC3.25 (A11), IC4.25 (A11), IC5.25 (A11), JP3.27, JP5.27, R44.1
B1_A12: IC1.4 (A12), IC3.4 (A12), IC4.4 (A12), IC5.4 (A12), JP3.29, JP5.29, R45.1
B1_A13: IC1.28 (A13), IC3.28 (A13), IC4.28 (A13), IC5.28 (A13), JP3.31, JP5.31, R46.1
B1_A14: IC1.3 (A14), IC3.3 (A14), IC4.3 (A14), IC5.3 (A14), JP3.33, JP5.33, R47.1
B1_A15: IC1.31 (A15), IC3.31 (A15), IC4.31 (A15), IC5.31 (A15), JP3.35, JP5.35, R49.1
B1_A16: IC1.2 (A16), IC3.2 (A16), IC4.2 (A16), IC5.2 (A16), JP3.6, JP5.6, R48.1
B1_A17: IC1.1 (A17), IC3.1 (A17), IC4.1 (A17), IC5.1 (A17), JP3.8, JP5.8, R50.1
B1_A18: IC1.30 (A18), IC3.30 (A18), IC4.30 (A18), IC5.30 (A18), JP3.10, JP5.10, R51.1
B1_A19: IC10.1 (A), JP3.12, JP5.12, R52.1
B1_A20: IC10.2 (B), JP3.14, JP5.14, R53.1
B1_A21: JP3.16, JP5.16, R54.1
B1_A22: JP3.18, JP5.18, R55.1
B1_A23: JP3.20, JP5.20, R56.1
B1_A24: JP3.22, JP5.22, R58.1
B1_A25: JP3.24, JP5.24, R57.1
B1_A26: JP3.26, JP5.26, R59.1
B1_A27: JP3.28, JP5.28, R60.1
B1_A28: JP3.30, JP5.30, R61.1
B1_A29: JP3.32, JP5.32, R62.1
B1_A30: JP3.34, JP5.34, R63.1
B1_A31: JP3.36, JP5.36, R64.1
B1_D0: IC1.13 (I/O0), IC3.13 (I/O0), IC4.13 (I/O0), IC5.13 (I/O0), JP4.6, JP6.6
B1_D1: IC1.14 (I/O1), IC3.14 (I/O1), IC4.14 (I/O1), IC5.14 (I/O1), JP4.8, JP6.8
B1_D2: IC1.15 (I/O2), IC3.15 (I/O2), IC4.15 (I/O2), IC5.15 (I/O2), JP4.10, JP6.10
B1_D3: IC1.17 (I/O3), IC3.17 (I/O3), IC4.17 (I/O3), IC5.17 (I/O3), JP4.12, JP6.12
B1_D4: IC1.18 (I/O4), IC3.18 (I/O4), IC4.18 (I/O4), IC5.18 (I/O4), JP4.14, JP6.14
B1_D5: IC1.19 (I/O5), IC3.19 (I/O5), IC4.19 (I/O5), IC5.19 (I/O5), JP4.16, JP6.16
B1_D6: IC1.20 (I/O6), IC3.20 (I/O6), IC4.20 (I/O6), IC5.20 (I/O6), JP4.18, JP6.18
B1_D7: IC1.21 (I/O7), IC3.21 (I/O7), IC4.21 (I/O7), IC5.21 (I/O7), JP4.20, JP6.20
CE0: IC8.22 (!CE), IC9.15 (Y0)
CE1: IC2.22 (!CE), IC9.14 (Y1)
CE2: IC6.22 (!CE), IC9.13 (Y2)
CE3: IC7.22 (!CE), IC9.12 (Y3)
CE4: IC5.22 (!CE), IC10.15 (Y0)
CE5: IC1.22 (!CE), IC10.14 (Y1)
CE6: IC3.22 (!CE), IC10.13 (Y2)
CE7: IC4.22 (!CE), IC10.12 (Y3)
GND: C1.1, C2.1, C3.1, C4.1, C5.1, C6.1, C7.1, C8.1, C9.1, C10.1, IC1.16 (GND), IC2.16 (GND), IC3.16 (GND), IC4.16 (GND), IC5.16 (GND), IC6.16 (GND), IC7.16 (GND), IC8.16 (GND), IC9.3 (C), IC9.4 (!G2A), IC9.5 (!G2B), IC9.8 (GND), IC10.3 (C), IC10.4 (!G2A), IC10.5 (!G2B), IC10.8 (GND), JP1.3, JP1.4, JP1.37, JP1.38, JP2.3, JP2.4, JP2.37, JP2.38, JP3.3, JP3.4, JP3.37, JP3.38, JP4.3, JP4.4, JP4.37, JP4.38, JP5.3, JP5.4, JP5.37, JP5.38, JP6.3, JP6.4, JP6.37, JP6.38, R1.2, R2.2, R3.2, R4.2, R5.2, R6.2, R7.2, R8.2, R9.2, R10.2, R11.2, R12.2, R13.2, R14.2, R15.2, R16.2, R17.2, R18.2, R19.2, R20.2, R21.2, R22.2, R23.2, R24.2, R25.2, R26.2, R27.2, R28.2, R29.2, R30.2, R31.2, R32.2, R33.2, R34.2, R35.2, R36.2, R37.2, R38.2, R39.2, R40.2, R41.2, R42.2, R43.2, R44.2, R45.2, R46.2, R47.2, R48.2, R49.2, R50.2, R51.2, R52.2, R53.2, R54.2, R55.2, R56.2, R57.2, R58.2, R59.2, R60.2, R61.2, R62.2, R63.2, R64.2
OE: IC1.24 (!OE), IC2.24 (!OE), IC3.24 (!OE), IC4.24 (!OE), IC5.24 (!OE), IC6.24 (!OE), IC7.24 (!OE), IC8.24 (!OE)
VCC: C1.2, C2.2, C3.2, C4.2, C5.2, C6.2, C7.2, C8.2, C9.2, C10.2, IC1.32 (VDD), IC2.32 (VDD), IC3.32 (VDD), IC4.32 (VDD), IC5.32 (VDD), IC6.32 (VDD), IC7.32 (VDD), IC8.32 (VDD), IC9.6 (G1), IC9.16 (VCC), IC10.6 (G1), IC10.16 (VCC), JP1.1, JP1.2, JP1.39, JP1.40, JP2.1, JP2.2, JP2.39, JP2.40, JP3.1, JP3.2, JP3.39, JP3.40, JP4.1, JP4.2, JP4.39, JP4.40, JP5.1, JP5.2, JP5.39, JP5.40, JP6.1, JP6.2, JP6.39, JP6.40
WE: IC1.29 (!WE), IC2.29 (!WE), IC3.29 (!WE), IC4.29 (!WE), IC5.29 (!WE), IC6.29 (!WE), IC7.29 (!WE), IC8.29 (!WE)

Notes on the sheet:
Memory group 0
Memory group 1
Chip selector
Passive Components
Headers
